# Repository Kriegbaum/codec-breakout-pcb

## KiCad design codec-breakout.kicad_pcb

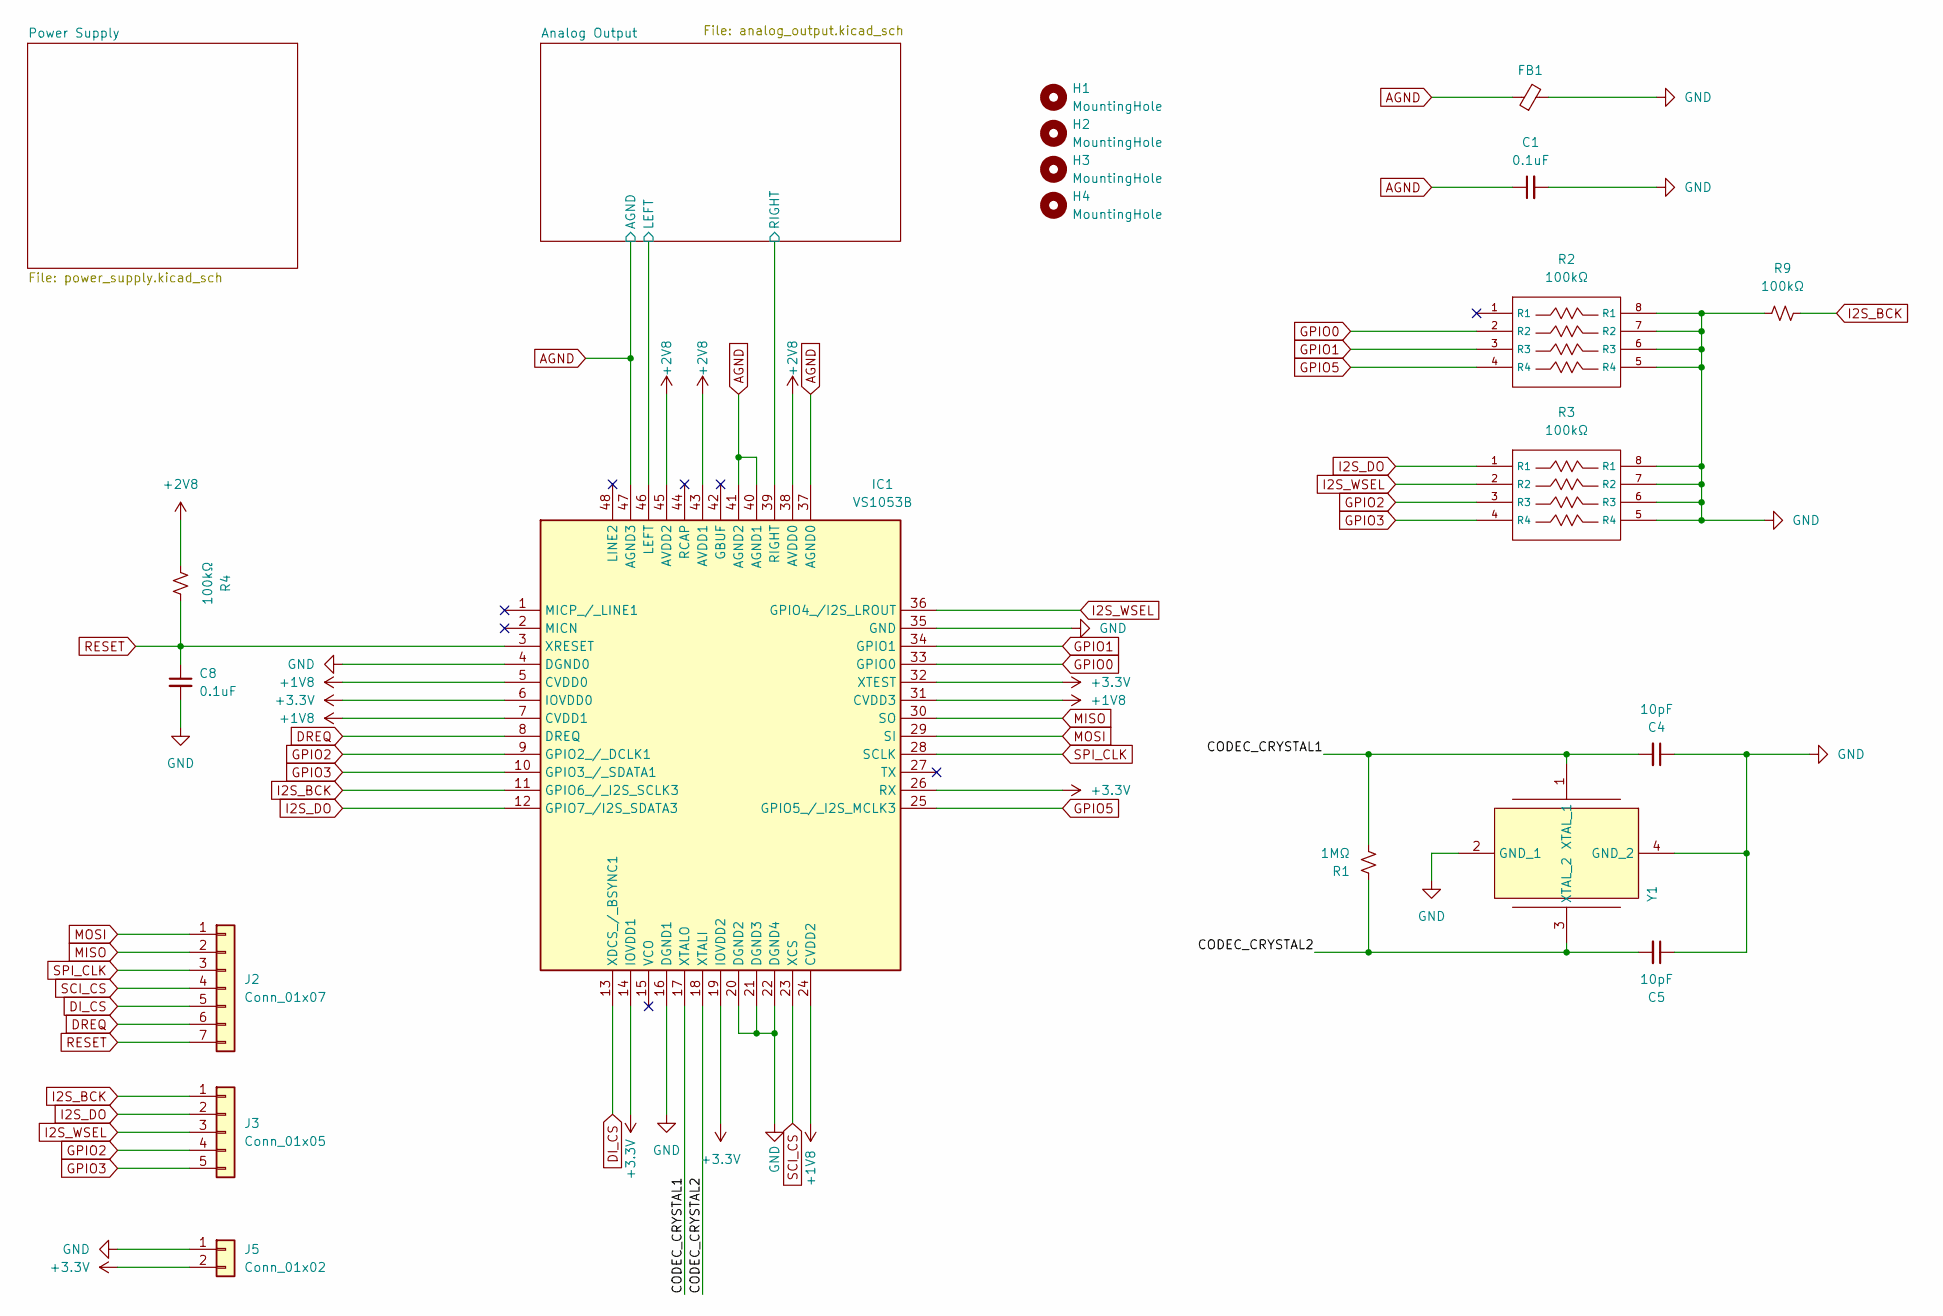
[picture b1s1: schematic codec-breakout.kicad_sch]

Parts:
C1, C8: CL21B104KBCNNNC; 0805_cap; Tolerance 10%; Voltage 50v
C4, C5: CL21C100CBANNNC; 0805_cap; Tolerance 10%; Voltage 50v
FB1: 2508053017Y3; L_0805_2012Metric_Pad1.15x1.40mm_HandSolder
H1, H2, H3, H4: MountingHole; MountingHole_3.2mm_M3_DIN965_Pad
IC1: VS1053B; VS1053; Manufacturer_Part_Number VS1053B
J2: Conn_01x07; PinHeader_1x07_P2.54mm_Vertical
J3: Conn_01x05; PinHeader_1x05_P2.54mm_Vertical
J5: Conn_01x02; PinHeader_1x02_P2.54mm_Vertical
R1: RC0805FR-101ML; R_0805_2012Metric_Pad1.20x1.40mm_HandSolder
R2, R3: YC124-JR-07100KL; Resistor_Array_0805_x4
R4, R9: ERA-6AEB104V; R_0805_2012Metric_Pad1.20x1.40mm_HandSolder
Y1: ABM8G-12.288MHZ-4Y-T3; ABM8G; Manufacturer_Part_Number ABM8G-12.288MHZ-4Y-T3; Mouser Part Number 815-ABM8G-12.28-4YT3

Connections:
+1V8: IC1.5 (CVDD0), IC1.7 (CVDD1), IC1.24 (CVDD2), IC1.31 (CVDD3); also elsewhere on the board
+2V8: IC1.38 (AVDD0), IC1.43 (AVDD1), IC1.45 (AVDD2), R4.1; also elsewhere on the board
+3.3V: IC1.6 (IOVDD0), IC1.14 (IOVDD1), IC1.19 (IOVDD2), IC1.26 (RX), IC1.32 (XTEST), J5.2; also elsewhere on the board
/Analog Output/LEFT: IC1.46 (LEFT); also elsewhere on the board
/Analog Output/RIGHT: IC1.39 (RIGHT); also elsewhere on the board
/CODEC_CRYSTAL1: C4.2, IC1.17 (XTALO), R1.2, Y1.1 (XTAL_1)
/CODEC_CRYSTAL2: C5.2, IC1.18 (XTALI), R1.1, Y1.3 (XTAL_2)
AGND: C1.1, FB1.1, IC1.37 (AGND0), IC1.40 (AGND1), IC1.41 (AGND2), IC1.47 (AGND3); also elsewhere on the board
DI_CS: IC1.13 (XDCS_/_BSYNC1), J2.5
DREQ: IC1.8 (DREQ), J2.6
GND: C1.2, C4.1, C5.1, C8.2, FB1.2, IC1.4 (DGND0), IC1.16 (DGND1), IC1.20 (DGND2), IC1.21 (DGND3), IC1.22 (DGND4), IC1.35 (GND), J5.1, R2.5 (R4), R2.6 (R3), R2.7 (R2), R2.8 (R1), R3.5 (R4), R3.6 (R3), R3.7 (R2), R3.8 (R1), R9.1, Y1.2 (GND_1), Y1.4 (GND_2); also elsewhere on the board
GPIO0: IC1.33 (GPIO0), R2.2 (R2)
GPIO1: IC1.34 (GPIO1), R2.3 (R3)
GPIO2: IC1.9 (GPIO2_/_DCLK1), J3.4, R3.3 (R3)
GPIO3: IC1.10 (GPIO3_/_SDATA1), J3.5, R3.4 (R4)
GPIO5: IC1.25 (GPIO5_/_I2S_MCLK3), R2.4 (R4)
I2S_BCK: IC1.11 (GPIO6_/_I2S_SCLK3), J3.1, R9.2
I2S_DO: IC1.12 (GPIO7_/I2S_SDATA3), J3.2, R3.1 (R1)
I2S_WSEL: IC1.36 (GPIO4_/I2S_LROUT), J3.3, R3.2 (R2)
MISO: IC1.30 (SO), J2.2
MOSI: IC1.29 (SI), J2.1
RESET: C8.1, IC1.3 (XRESET), J2.7, R4.2
SCI_CS: IC1.23 (XCS), J2.4
SPI_CLK: IC1.28 (SCLK), J2.3

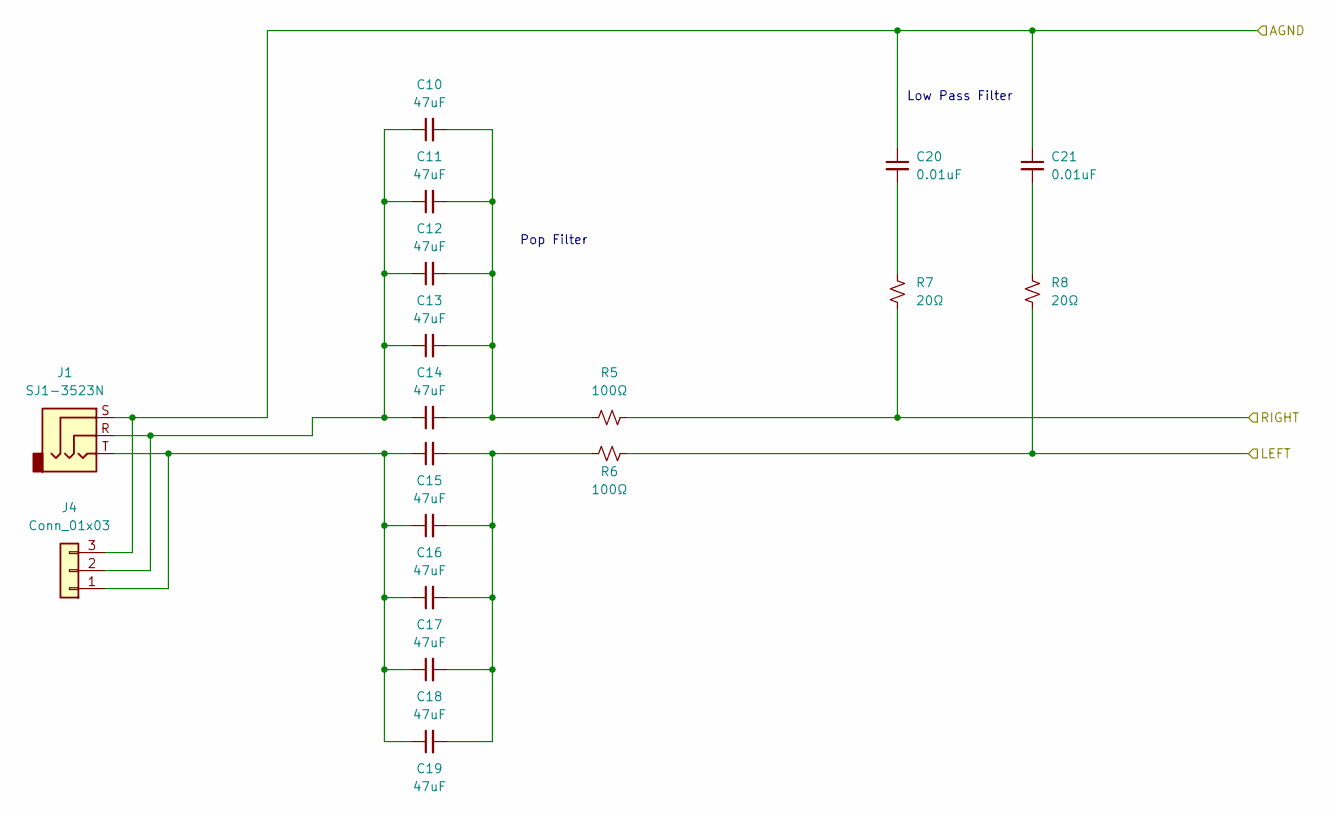
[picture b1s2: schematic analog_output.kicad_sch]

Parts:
C10, C11, C12, C13, C14, C15, C16, C17, C18, C19: CL21A476MQYNNNE; 0805_cap; Tolerance 20%; Voltage 6.3v
C20, C21: CL21B103KBANNNC; 0805_cap; Tolerance 10%; Voltage 50v
J1: SJ1-3523N; Jack_3.5mm_CUI_SJ1-3523N_Horizontal
J4: Conn_01x03; PinHeader_1x03_P2.54mm_Vertical
R5, R6: RC0805FR-07100RL; R_0805_2012Metric_Pad1.20x1.40mm_HandSolder
R7, R8: RC0805JR-0720RL; R_0805_2012Metric_Pad1.20x1.40mm_HandSolder

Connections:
/Analog Output/LEFT: R6.2, R8.2; also elsewhere on the board
/Analog Output/RIGHT: R5.2, R7.2; also elsewhere on the board
AGND: C20.1, C21.1, J1.S, J4.3; also elsewhere on the board
unnamed: C10.2, C11.2, C12.2, C13.2, C14.2, R5.1
unnamed: C15.2, C16.2, C17.2, C18.2, C19.2, R6.1
unnamed: C20.2, R7.1
unnamed: C21.2, R8.1
unnamed: C15.1, C16.1, C17.1, C18.1, C19.1, J1.T, J4.1
unnamed: C10.1, C11.1, C12.1, C13.1, C14.1, J1.R, J4.2

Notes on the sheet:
Pop Filter
Low Pass Filter

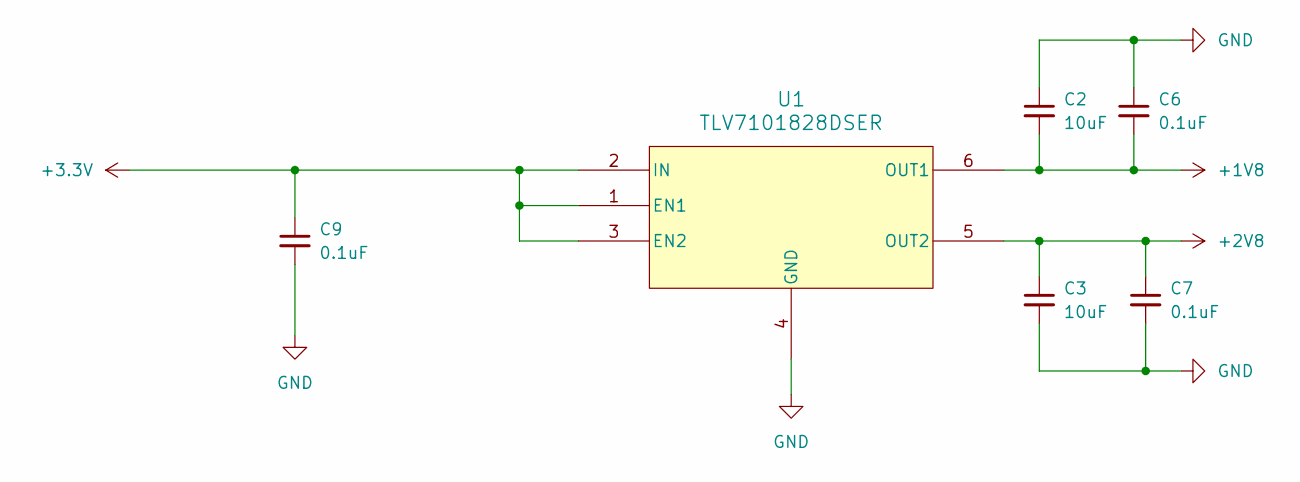
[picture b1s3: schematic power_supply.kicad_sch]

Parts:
C2, C3: CL21A106KOQNNNE; 0805_cap; Tolerance 20%; Voltage 16v
C6, C7, C9: CL21B104KBCNNNC; 0805_cap; Tolerance 10%; Voltage 50v
U1: TLV7101828DSER

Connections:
+1V8: C2.2, C6.2, U1.6 (OUT1); also elsewhere on the board
+2V8: C3.1, C7.1, U1.5 (OUT2); also elsewhere on the board
+3.3V: C9.1, U1.1 (EN1), U1.2 (IN), U1.3 (EN2); also elsewhere on the board
GND: C2.1, C3.2, C6.1, C7.2, C9.2, U1.4 (GND); also elsewhere on the board

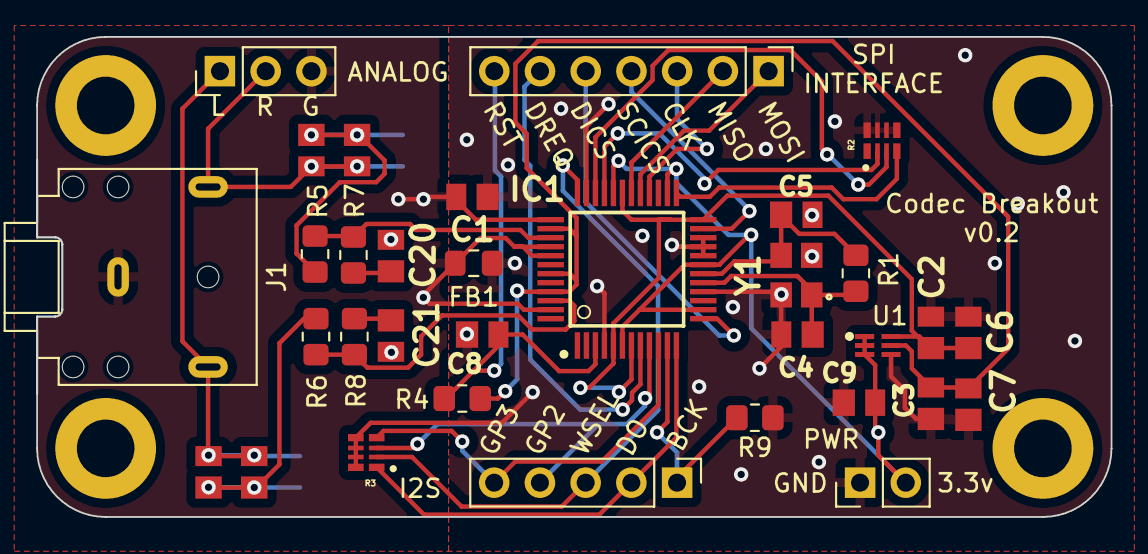
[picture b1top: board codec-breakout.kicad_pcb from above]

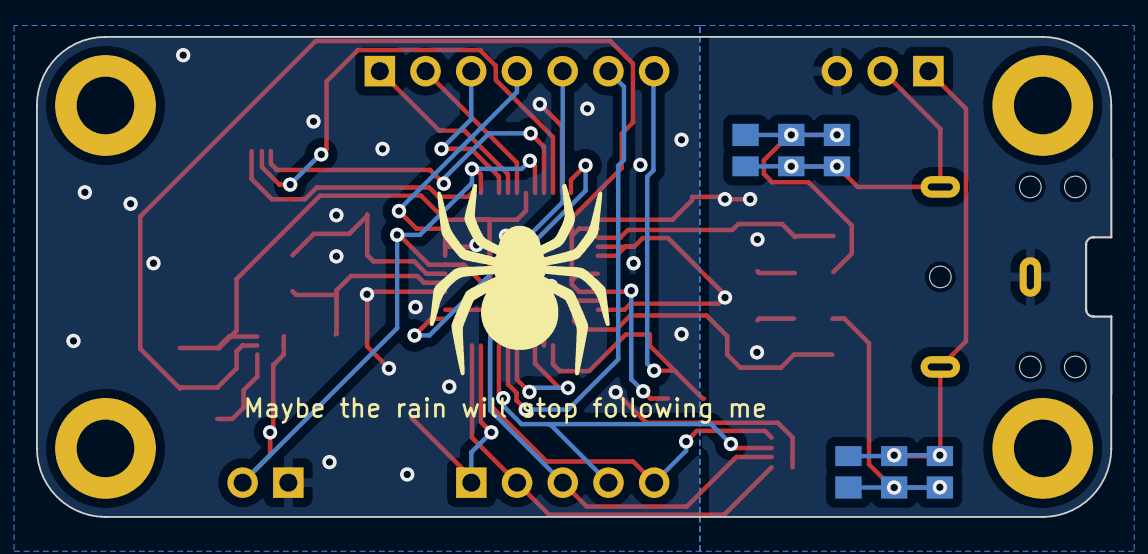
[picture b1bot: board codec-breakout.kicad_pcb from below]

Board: 2 copper layers, 59.7 x 26.6 mm, 43 parts (6 on the bottom side), 30 nets.

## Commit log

2023-08-09 Fix incorrect silkscreen
